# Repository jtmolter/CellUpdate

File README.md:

# CellUpdate
Hardware files of NewCellTracker for UMDBPP, to be merged into a complete folder later

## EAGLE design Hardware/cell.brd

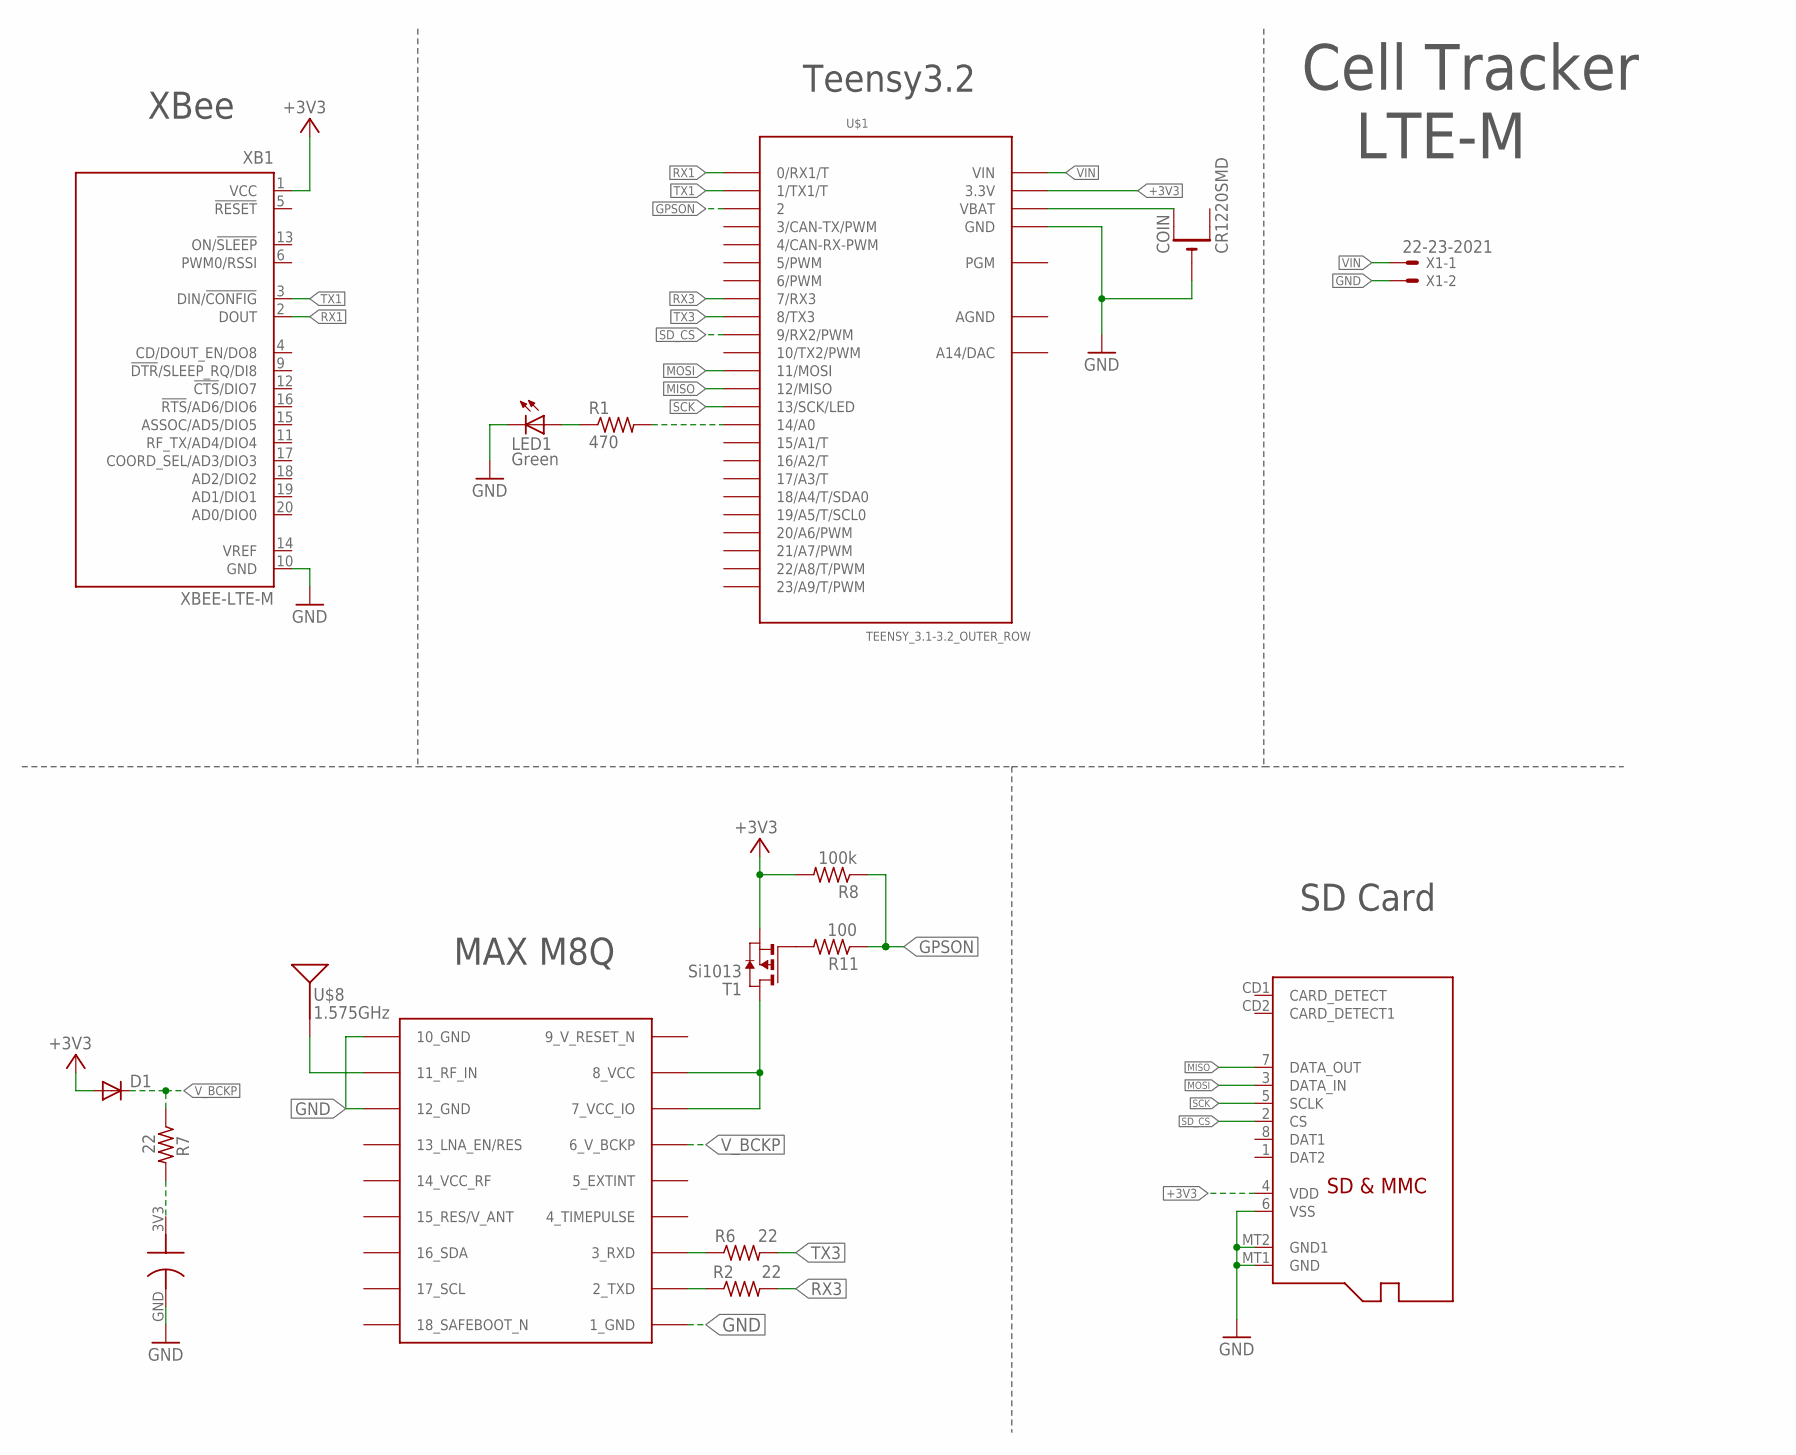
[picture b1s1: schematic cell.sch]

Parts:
C1: DCK-3R3E204T614-E; ELNASUPERCAP
COIN: CR1220SMD; CR1220-SMD
D1: DIODE-SOD523; SOD523
LED1: Green; CHIP-LED0603
R1: 470; R0603
R2, R6, R7: 22; R0603
R8: 100k; R0603
R11: 100; R0603
T1: Si1013; SOT-23
U$1: TEENSY_3.1-3.2_OUTER_ROW; TEENSY_3.0-3.2&LC_OUTER_ROW
U$2: MICROSD
U$7: MAX-M8
U$8: 1.575GHz; SPARKFUN-GPS_ANT-GPS-2X7MM
X1: 22-23-2021
XB1: XBEE-LTE-M; XBEE-PRO

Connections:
9_V_RESET_N: U$7.9_RESET_N (9_V_RESET_N)
+3V3: D1.A, R8.2, T1.2 (S), U$1.3.3V, U$1.3.3V1 (3.3V), U$2.4 (VDD), XB1.1 (VCC)
AGND: U$1.AGND
GND: C1.GND, COIN.-, LED1.C, U$1.GND, U$1.GND1 (GND), U$2.6 (VSS), U$2.MT1 (GND), U$2.MT2 (GND1), U$7.1_GND, U$7.10_GND, U$7.12_GND, X1.2, XB1.10 (GND)
GPSON: R8.1, R11.1, U$1.2
MISO: U$1.12 (12/MISO), U$2.7 (DATA_OUT)
MOSI: U$1.11 (11/MOSI), U$2.3 (DATA_IN)
unnamed: U$7.11_RF_IN, U$8.1
unnamed: R1.2, U$1.14/A0
unnamed: R6.1, U$7.3_RXD
unnamed: R2.1, U$7.2_TXD
unnamed: R11.2, T1.3 (G)
unnamed: LED1.A, R1.1
unnamed: T1.1 (D), U$7.7_VCC_IO, U$7.8_VCC
unnamed: COIN.+$1 (+), U$1.VBAT
unnamed: C1.3V3, R7.2
RX1: U$1.0 (0/RX1/T), XB1.2 (DOUT)
RX3: R2.2, U$1.7 (7/RX3)
SCK: U$1.13 (13/SCK/LED), U$2.5 (SCLK)
SD_CS: U$1.9 (9/RX2/PWM), U$2.2 (CS)
TX1: U$1.1 (1/TX1/T), XB1.3 (DIN/!CONFIG)
TX3: R6.2, U$1.8 (8/TX3)
VIN: U$1.VIN, X1.1
V_BCKP: D1.C, R7.1, U$7.6_V_BCKP

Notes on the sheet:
MAX M8Q
SD Card
XBee
Teensy3.2
Cell Tracker LTE-M

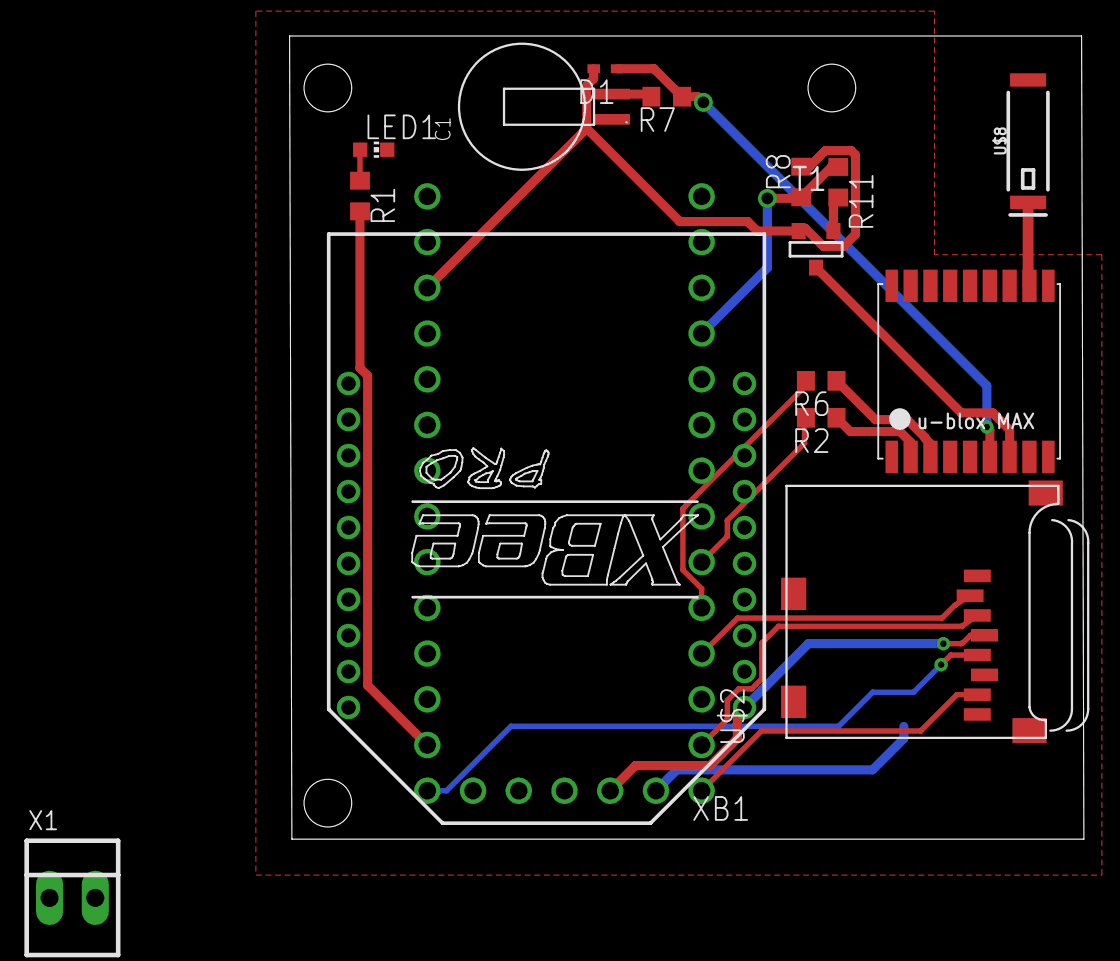
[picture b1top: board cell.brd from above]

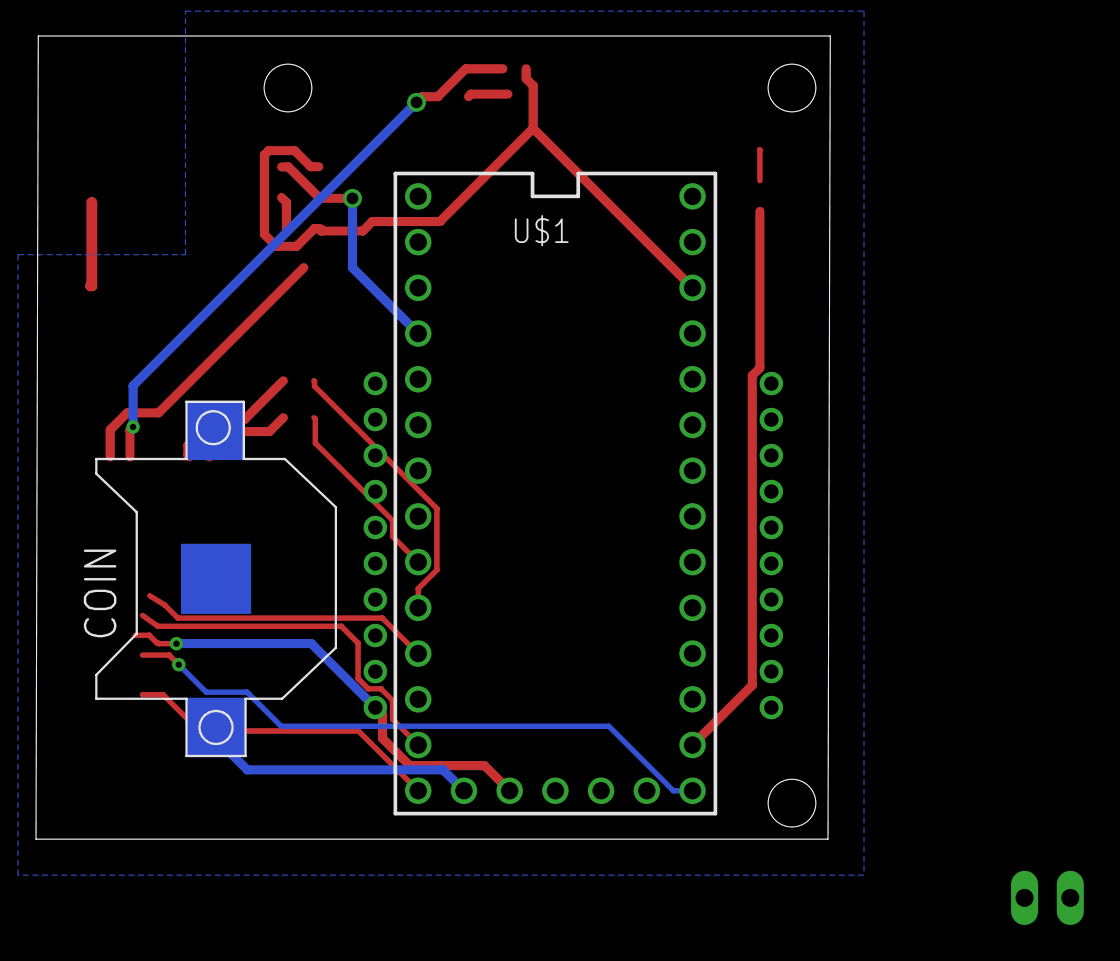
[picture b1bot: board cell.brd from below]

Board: 2 copper layers, 44.1 x 44.6 mm, 17 parts (2 on the bottom side), 22 nets.

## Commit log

2019-07-27 First push of cell hardware
2019-07-27 Moving things and considering a regulator
2020-01-06 Formatting
